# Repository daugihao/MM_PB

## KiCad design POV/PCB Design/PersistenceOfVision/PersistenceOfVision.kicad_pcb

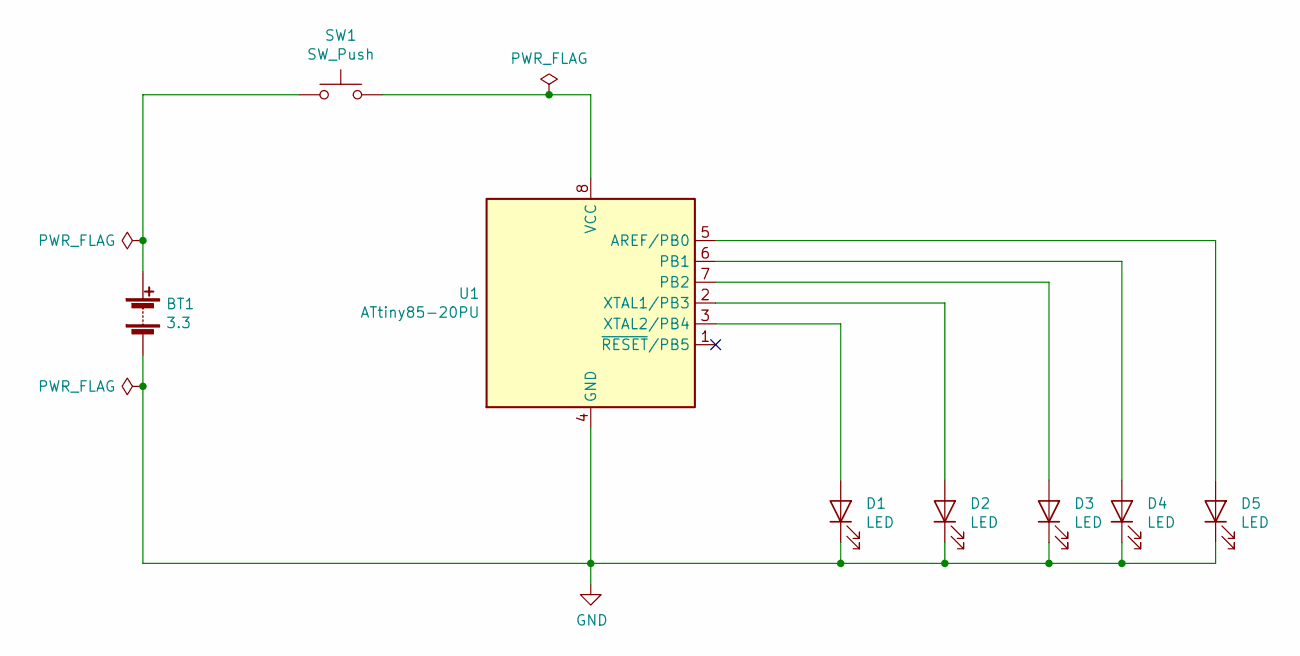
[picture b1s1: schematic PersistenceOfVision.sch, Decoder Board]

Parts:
BT1: 3.3; BatteryHolder_Keystone_1060_1x2032
D1, D2, D3, D4, D5: LED; LED_D5.0mm
SW1: SW_Push; SW_PUSH-12mm
U1: ATtiny85-20PU; DIP-8_W7.62mm

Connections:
GND: BT1.2 (-), D1.1 (K), D2.1 (K), D3.1 (K), D4.1 (K), D5.1 (K), U1.4 (GND)
unnamed: BT1.1 (+), SW1.1
unnamed: D1.2 (A), U1.3 (XTAL2/PB4)
unnamed: D2.2 (A), U1.2 (XTAL1/PB3)
unnamed: D3.2 (A), U1.7 (PB2)
unnamed: D4.2 (A), U1.6 (PB1)
unnamed: D5.2 (A), U1.5 (AREF/PB0)
unnamed: SW1.2, U1.8 (VCC)

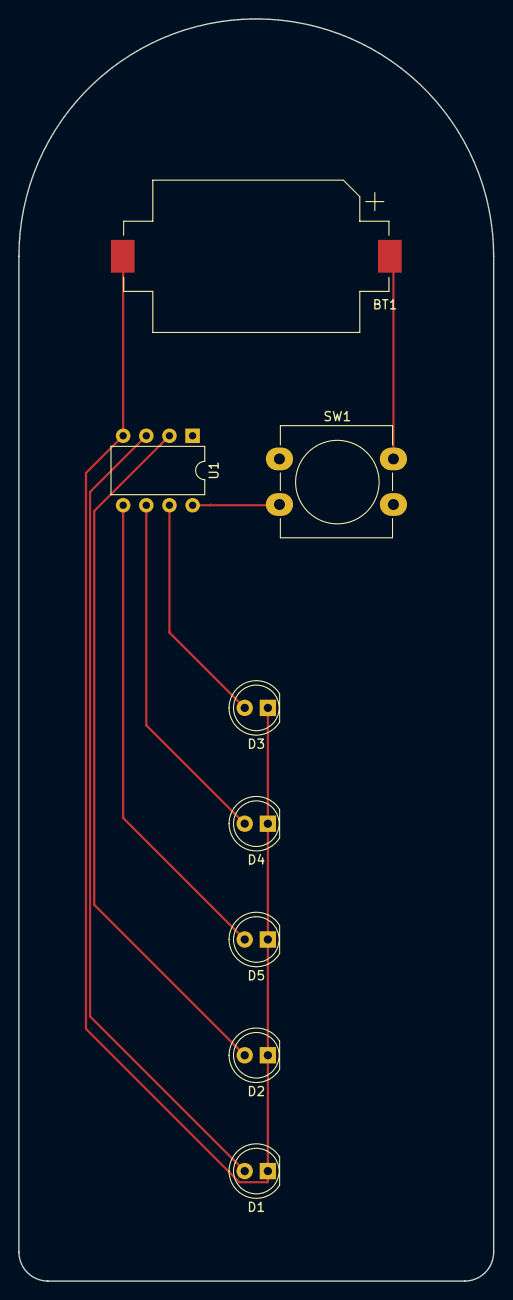
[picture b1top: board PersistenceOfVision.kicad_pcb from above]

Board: 2 copper layers, 52.1 x 138.4 mm, 8 parts (0 on the bottom side), 8 nets.

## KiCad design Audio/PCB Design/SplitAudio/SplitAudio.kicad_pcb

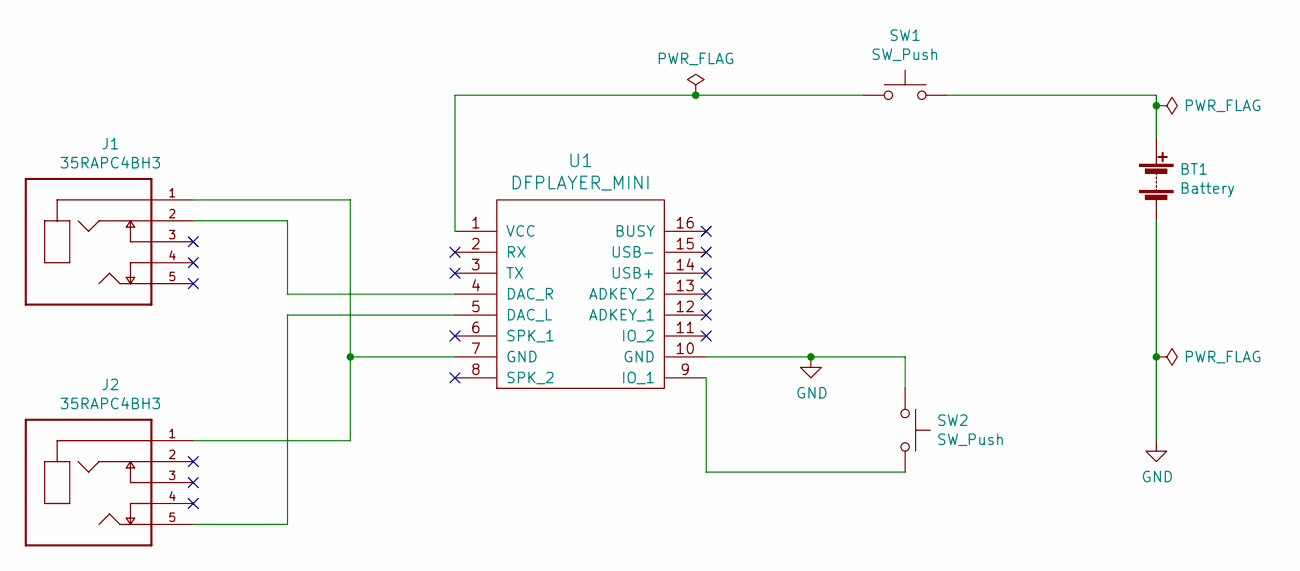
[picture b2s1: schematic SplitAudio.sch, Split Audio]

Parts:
BT1: Battery; BatteryHolder_Keystone_1060_1x2032
J1, J2: 35RAPC4BH3; SWITCHCRAFT_35RAPC4BH3
SW1, SW2: SW_Push; SW_PUSH-12mm_Wuerth-430476085716
U1: DFPLAYER_MINI; DFPlayer_Mini

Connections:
GND: BT1.2 (-), SW2.1, U1.10 (GND)
unnamed: BT1.1 (+), SW1.2
unnamed: J1.1, J2.1, U1.7 (GND)
unnamed: J1.2, U1.4 (DAC_R)
unnamed: J2.5, U1.5 (DAC_L)
unnamed: SW1.1, U1.1 (VCC)
unnamed: SW2.2, U1.9 (IO_1)

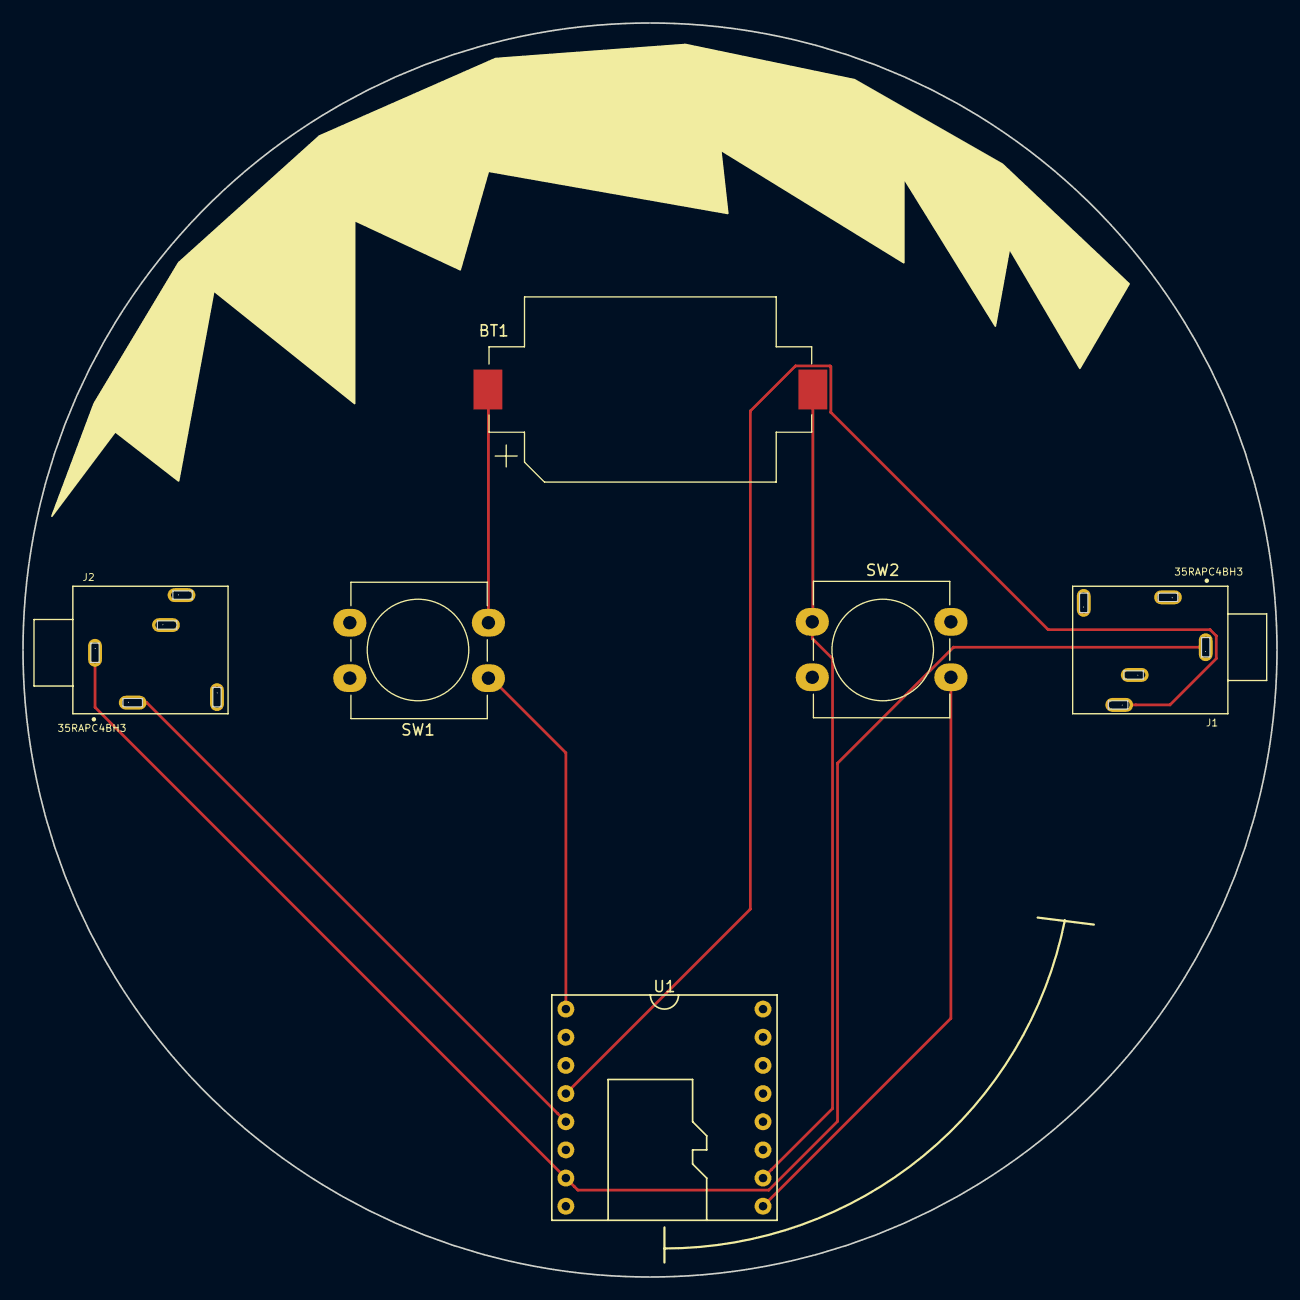
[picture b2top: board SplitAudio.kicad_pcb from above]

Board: 2 copper layers, 113.1 x 113.1 mm, 6 parts (0 on the bottom side), 7 nets.

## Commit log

2019-02-19 Added Instructables design
2019-02-19 Create basic new circuit board
2019-02-19 Added graphics to the board
2019-02-19 Updated to new button with wider holes
2019-02-19 Created Gerber files
2019-02-20 Reproduced Gerber files
2019-02-20 Initial partially complete board
2019-02-20 Audio board completed
2019-02-20 Zip file
2019-03-08 Corrected LED order in numbering
2019-03-08 Switched order of LEDs, increased the delay and made it spell 'atoyota'
2019-03-11 Changed details on schematic for puzzle manual
2019-03-21 Renamed board
2019-03-22 Created PCB stencil puzzle for Battersea Power Station
2019-05-28 Moved PoV code and work to a separate repo
